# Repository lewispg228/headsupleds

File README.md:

# headsupleds
While flying my RC airplane line-of-sight, I want to know some data from the plane (battery voltage, airspeed, turn coordination, G-forces). Maybe I can display this data in real time with some LEDs located in my peripheral vision. I'm gonna clip some electronics to my sunglasses and see how this goes :)

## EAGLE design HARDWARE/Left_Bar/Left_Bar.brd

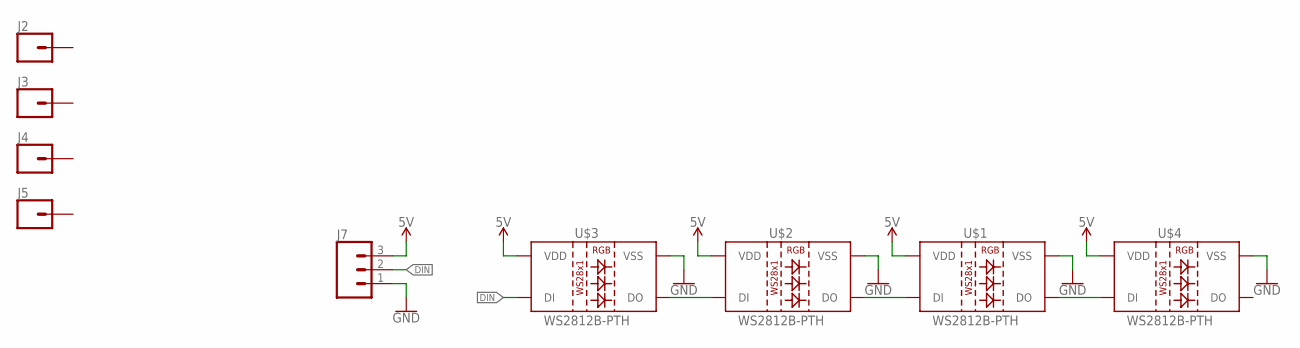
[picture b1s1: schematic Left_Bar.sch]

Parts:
J2, J3, J4, J5: CONN_01OFFSET; 1X01_OFFSET
J7: CONN_03; 1X03
U$1, U$2, U$3, U$4: WS2812B-PTH; WS2812B-PTH-KIT

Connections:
5V: J7.3, U$1.2 (VDD), U$2.2 (VDD), U$3.2 (VDD), U$4.2 (VDD)
DIN: J7.2, U$3.1 (DI)
GND: J7.1, U$1.3 (VSS), U$2.3 (VSS), U$3.3 (VSS), U$4.3 (VSS)
unnamed: U$1.4 (DO), U$4.1 (DI)
unnamed: U$2.1 (DI), U$3.4 (DO)
unnamed: U$1.1 (DI), U$2.4 (DO)

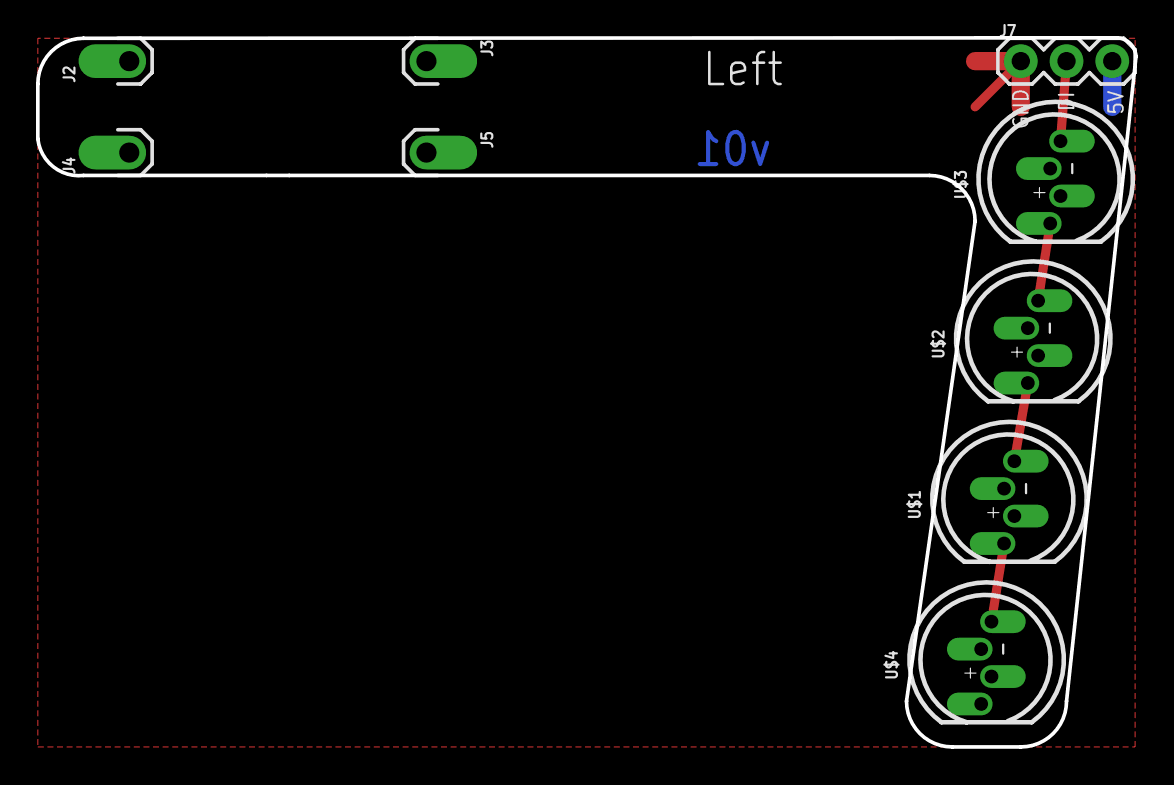
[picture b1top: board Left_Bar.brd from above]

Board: 2 copper layers, 61.0 x 39.4 mm, 9 parts (0 on the bottom side), 6 nets.

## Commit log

2018-01-14 calibrating adc vals to real voltages
2018-01-14 Got ADC value coming in
    example 1 is base, exampe 2 is plane,
    currently sending ADC value every 10 ms... this might be a higher
    frequency than necessary, but heck let see what it can do.
2018-01-15 LED controller working, base (ex 1) test commands working
2018-01-15 Getting close. Still need to fine tune adc mapping to voltage
    Note, I am planning on mapping the ADV for batt readings to a voltage.
    Rather than using floats, I am just using a 3 digit int. 126 actually
    means 12.6V.
2018-01-17 initial drawings for the turn coordinator sensor
    The plan is to make a diy "frictionless" rotational sensor. This disc
    will be attached to a freely rotating rod. The rod will go upward out of
    the top of the fuse (or wing maybe) and have a stiff flag attached to it
    (acting like a fin or rudder). This will get held into position by the
    oncoming airflow and rotate to either side to sense coordination. Much
    like a yaw string on a glider. This disc will rotate above an analog
2018-01-17 created jpg version for printing
2018-01-18 Set 12.6 and 11.1 adc values
    Using a power supply, I sent 12/6V and 11.1V at it, and plugged in those reading into the MAP function. Seems to accurately show voltage. wahoo!
2018-01-18 added in "status" blink
    every 100 messages, it will kill all LEDs to indicate that it's still getting stuff from the plane.
2018-01-18 pic of controller and leds - prototype 1
2018-08-01 Starting a custom PCBs to hold LEDs on sunglasses
2018-08-07 heads up leds with ws2812s - v01
2018-08-17 testing out protos with some simple code
2018-08-17 fixed ws2812 pinouts - added res and cap
    library for ws2812 pth pinout was incorrect. I also added in a cap and resistor like the hookup guide suggests. Not sure if necessary, cuz the protos of v01 are working without (although I had to rot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
2018-09-10 original scan of top down view of sun glasses
    gonna use this to further match up pcb with actual sunglasses.
2018-09-10 glasses into eagle library work
2018-09-10 renames right and left, finished left
2018-09-10 left bar v01 correction
2018-09-21 more testing code

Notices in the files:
parts and their libraries:
SparkFun-Connectors: Licensing: Creative Commons ShareAlike 4.0 International - https://creativecommons.org/licenses/by-sa/4.0
